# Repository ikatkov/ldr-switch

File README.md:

# Tiny LDR switch

Based on $0.60 Attiny13 MCU. 1kB flash, 256B ram.

It turns ON when it's dark (user configurable), stays ON for X hours, turns OFF, and waits till it's dark again. Intended to use with a battery, so it only consumes 5uA. Watch out for input power voltage. Min is 1.8V max is 5.5V. Max load current ~2A. Exceeds this and PCB traces will heat up and unsolder components.
There is simple diode craw-bar reverse voltage protection for MCU.

# Manufacturing

[PCB](./kicad/main.step)

[Enclosure lid](lid.stl)

[Enclosure base](base.stl)

# Code

MCU sleeps all the time. Wakes up via watchdog interrupt every 4 sec to measure light. It powers the LDR/R voltage divider via the MCU pin, takes ADC measurements, and turns off the pin to save power. Compares measured light with the thresholds and goes into ON, OFF, or WAIT_FOR_RESET state. Depending on the state, it turns the load ON/OFF.
A short button press wakes it from sleep, forcing it to measure light. 

* If it was in the OFF state - record the new "dark" light threshold, turn the load ON, start the auto-turn-off timer, and go into the ON state.
* If it was in the ON state - it turns the load OFF and goes into the WAIT_FOR_RESET state.

A long button press lets you set the auto-turn-off timer duration. Keep the button pressed and watch the LOAD blink. 1 blink == 1 hour, 2 blinks == 2 hours etc. Release the button once the desired number of hours is indicated. 

When the timer is UP, the load turns OFF, and the MCU transitions into the WAIT_FOR_RESET state.

There are two light thresholds in the code. 

* "dark" - once it's darker than this, MCU turns the load ON and goes into the ON state
* "bright" - once it's brighter than this, MCU goes from  WAIT_FOR_RESET into the OFF state. 

WAIT_FOR_RESET is meant to capture the daytime reset so that the switch is only active once per day for X hours.

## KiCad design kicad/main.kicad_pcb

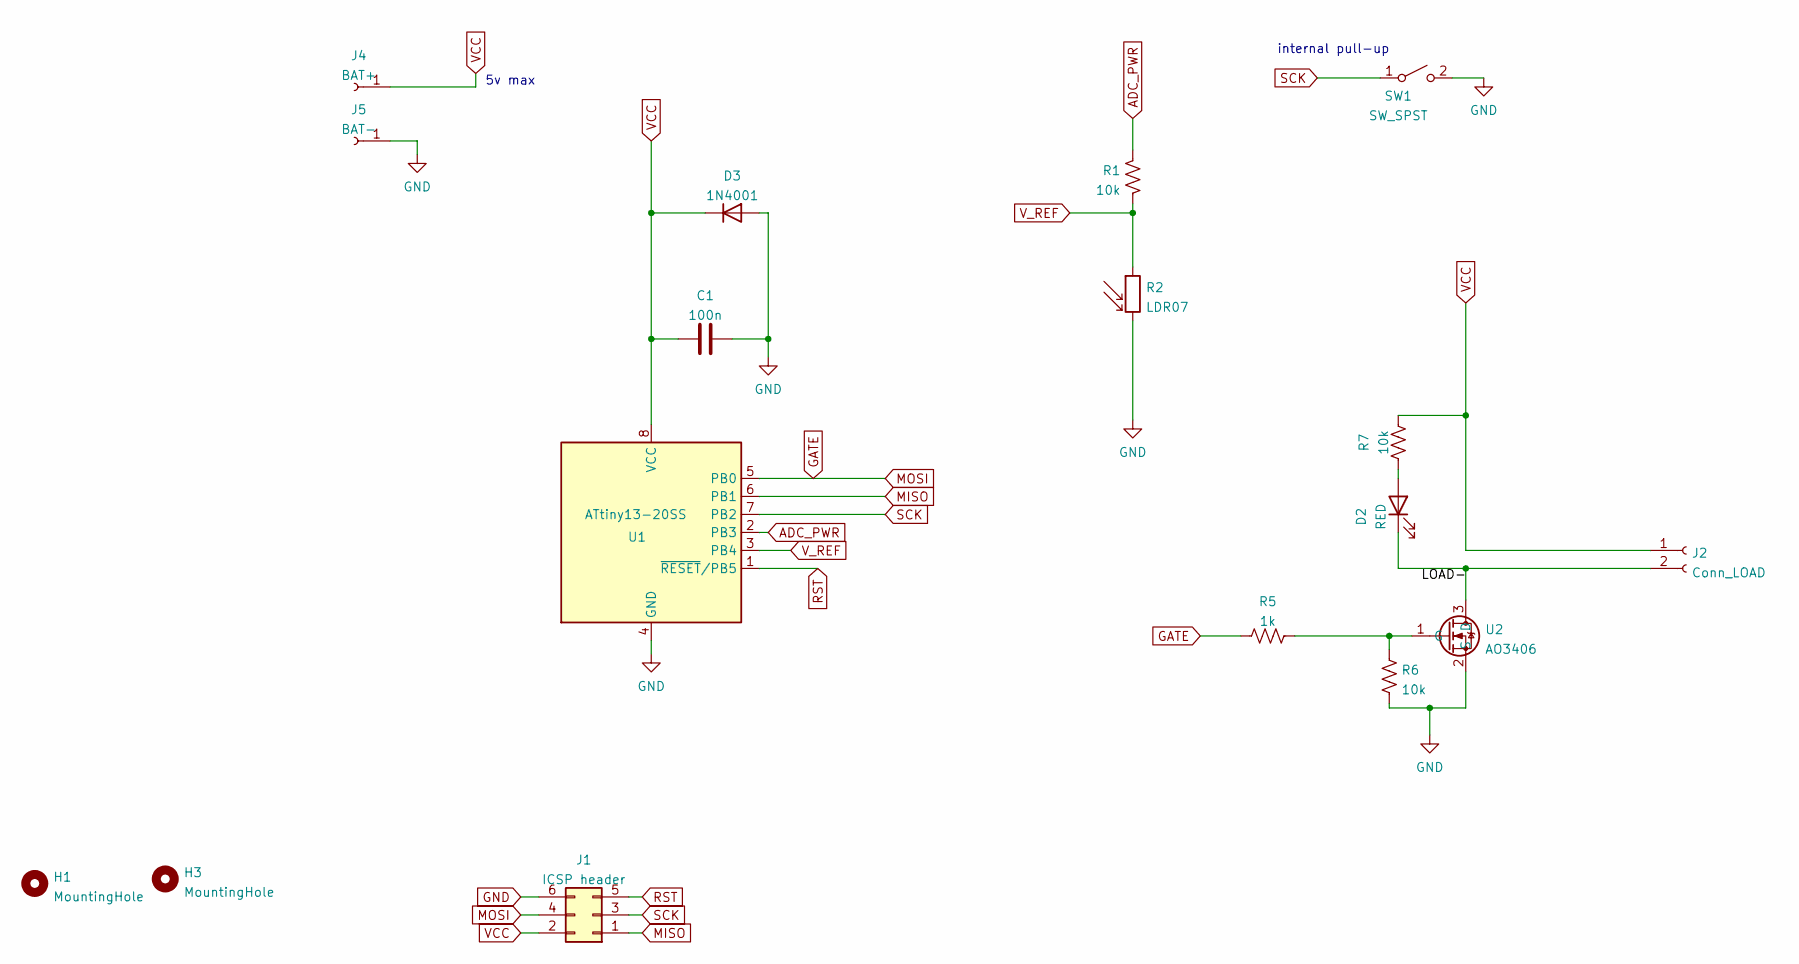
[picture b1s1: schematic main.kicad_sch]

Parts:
C1: 100n; C_1206_3216Metric
D2: RED; LED_0805_2012Metric
D3: 1N4001; D_SMA
H1, H3: MountingHole; MountingHole_2.2mm_M2
J1: ICSP header; PinHeader_2x03_P2.54mm_Vertical
J2: Conn_LOAD; JST_XH_B2B-XH-A_1x02_P2.50mm_Vertical
J4: BAT+; Pin_D1.0mm_L10.0mm
J5: BAT-; Pin_D1.0mm_L10.0mm
R1, R6, R7: 10k; R_0805_2012Metric
R2: LDR07; R_LDR_5.1x4.3mm_P3.4mm_Vertical
R5: 1k; R_0805_2012Metric
SW1: SW_SPST; SW_PUSH_6mm
U1: ATtiny13-20SS; SOIC-8_3.9x4.9mm_P1.27mm
U2: AO3406; SOT-23

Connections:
ADC_PWR: R1.2, U1.2 (PB3)
GATE: J1.4, R5.2, U1.5 (PB0)
GND: C1.2, D3.2 (A), J5.1, R2.2, R6.1, SW1.2 (B), U1.4 (GND), U2.2 (S)
MISO: J1.1, U1.6 (PB1)
unnamed: D2.1 (K), J2.2, U2.3 (D)
unnamed: D2.2 (A), R7.1
unnamed: R5.1, R6.2, U2.1 (G)
RST: J1.5, U1.1 (~RESET/PB5)
SCK: J1.3, SW1.1 (A), U1.7 (PB2)
VCC: C1.1, D3.1 (K), J1.2, J2.1, J4.1, R7.2, U1.8 (VCC)
V_REF: R1.1, R2.1, U1.3 (PB4)

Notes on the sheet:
internal pull-up
5v max

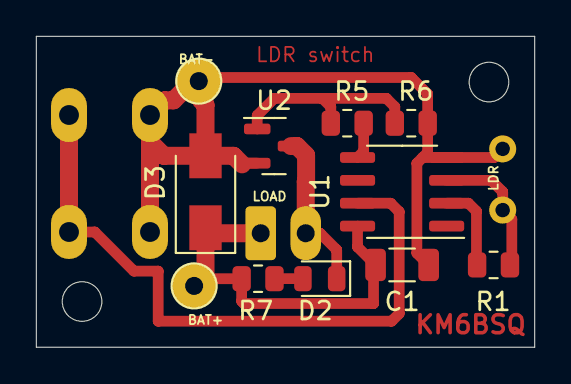
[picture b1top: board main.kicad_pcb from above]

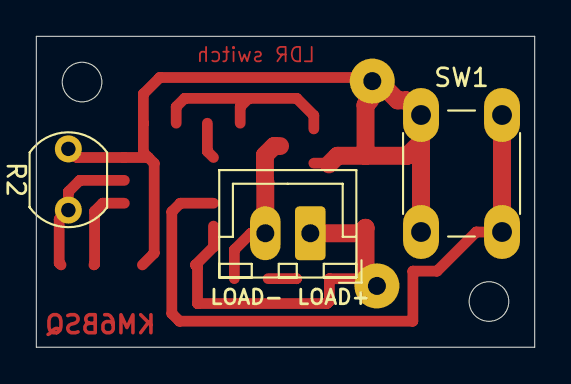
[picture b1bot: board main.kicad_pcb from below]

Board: 4 copper layers, 27.7 x 17.3 mm, 16 parts (3 on the bottom side), 9 nets.

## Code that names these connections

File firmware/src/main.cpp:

#include "Arduino.h"
#include <EEPROM.h>
#include <avr/sleep.h>
#include <avr/wdt.h>

static uint8_t lighOnDurationHours = 2;

#define LOAD_PIN PB0      // pin5 Attiny13
#define ADC_POWER_PIN PB3 //  pin2 on Attiny13
#define ADC_PIN A2        // PB4, pin3 Attiny13
#define INT_PIN PB2       // also button pin, pin7 Attiny13

static uint16_t lightThresholdDark = 700;
#define lightThresholdBright 350
#define LIGHT_THRESHOLD_HYSTERESIS 10

static enum state_t {
    OFF,
    ON,
    WAIT_FOR_RESET
} STATE;

static int32_t timer_sec = 0;

template <class T>
int EEPROM_writeAnything(int address, const T &value)
{
    const byte *p = (const byte *)(const void *)&value;
    uint8_t i;
    for (i = 0; i < sizeof(value); i++)
        EEPROM.write(address++, *p++);
    return i;
}

template <class T>
int EEPROM_readAnything(int address, T &value)
{
    byte *p = (byte *)(void *)&value;
    uint16_t i;
    for (i = 0; i < sizeof(value); i++)
        *p++ = EEPROM.read(address++);
    return i;
}

void powerDown(uint8_t sleepTime);
void blink(uint8_t times, uint16_t delayTime = 200);
void configureButtonInterrupt(bool enable);

EMPTY_INTERRUPT(PCINT0_vect);
EMPTY_INTERRUPT(WDT_vect)

void setlighOnDurationHours()
{
    uint8_t counter = 0;
    while (digitalRead(INT_PIN) == LOW)
    {
        counter++;
        if (counter > 8)
            counter = 1;
        blink(counter);
        delay(2000);
    }
    if (counter > 0 && counter != lighOnDurationHours)
    {
        lighOnDurationHours = counter;
        EEPROM_writeAnything(2, lighOnDurationHours);
    }
}

void readButton(uint16_t lightLevel)
{
    if (digitalRead(INT_PIN) == LOW)
    {
        if (STATE == ON)
        {
            digitalWrite(LOAD_PIN, LOW);
            STATE = WAIT_FOR_RESET;
            delay(2000); // debounce
        }
        else if (STATE == OFF || STATE == WAIT_FOR_RESET)
        {
            STATE = ON;
            blink(lighOnDurationHours);
            delay(1000); // blink delay + debounce
            digitalWrite(LOAD_PIN, HIGH);
            timer_sec = lighOnDurationHours * 60 * 60;

            // set new lightThresholdDark
            lightThresholdDark = lightLevel;

            EEPROM_writeAnything(0, lightThresholdDark);
        }
        setlighOnDurationHours();
    }
}

void powerDown(uint8_t sleepTime)
{
    ADCSRA &= ~(1 << ADEN); // adc OFF
    wdt_enable(sleepTime);  // watchdog
    WDTCR |= _BV(WDTIE);

    do
    {
        set_sleep_mode(SLEEP_MODE_PWR_DOWN);
        cli(); // Disable interrupts
        sleep_enable();
        sleep_bod_disable();
        sei(); // Enable interrupts
        sleep_cpu();

        sleep_disable();
        sei();
    } while (0);

    ADCSRA |= (1 << ADEN); // adc ON
}

void blink(uint8_t times, uint16_t delayTime)
{
    for (int i = times; i > 0; i--)
    {
        digitalWrite(LOAD_PIN, HIGH);
        delay(delayTime);
        digitalWrite(LOAD_PIN, LOW);
        delay(delayTime);
        wdt_reset();
    }
}

void setup()
{
    pinMode(ADC_POWER_PIN, OUTPUT);
    pinMode(ADC_PIN, INPUT);        // ADC
    pinMode(INT_PIN, INPUT_PULLUP); // button
    pinMode(LOAD_PIN, OUTPUT);      // gate

    analogReference(DEFAULT);

    cli();
    GIMSK |= _BV(PCIE);   //  Enable PCINT interrupt in the general interrupt mask
    PCMSK |= _BV(PCINT2); // Enable interrupt handler (ISR) for our chosen interrupt pin (PCINT2/PB2/pin 7)
    sei();

    EEPROM_readAnything(0, lightThresholdDark);
    if (lightThresholdDark < 0 || lightThresholdDark > 1024)
    {
        lightThresholdDark = 700;
        EEPROM_writeAnything(0, lightThresholdDark);
    }
    EEPROM_readAnything(2, lighOnDurationHours);
    if (lighOnDurationHours < 1 || lighOnDurationHours > 8)
    {
        lighOnDurationHours = 2;
    }

    blink(lighOnDurationHours);
}

void loop()
{
    digitalWrite(ADC_POWER_PIN, HIGH);
    uint16_t lightLevel = analogRead(ADC_PIN);
    digitalWrite(ADC_POWER_PIN, LOW);
    readButton(lightLevel);

    if (STATE == WAIT_FOR_RESET && lightLevel <= lightThresholdBright)
    {
        STATE = OFF;
    }

    if (STATE == OFF && lightLevel >= lightThresholdDark)
    {
        digitalWrite(LOAD_PIN, HIGH);
        timer_sec = lighOnDurationHours * 60 * 60;
        STATE = ON;
    }
    else if (STATE == ON && timer_sec <= 0)
    {
        digitalWrite(LOAD_PIN, LOW);
        STATE = WAIT_FOR_RESET;
    }
    else if (STATE == ON && lightLevel < lightThresholdDark - LIGHT_THRESHOLD_HYSTERESIS)
    {
        digitalWrite(LOAD_PIN, LOW);
        STATE = OFF;
    }

    powerDown(WDTO_4S);
    if (timer_sec > 0)
    {
        timer_sec -= 4;
    }
}

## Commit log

2022-11-09 code is broken, pcb OK
2022-11-09 working code, lots of comments
2022-11-09 attiny13 changes
2022-11-10 light duration settings
2022-11-10 clean up
2022-11-10 add README description and images
2022-11-10 grammar
2022-11-10 readme update
2022-11-10 add enclosure files
2022-11-10 link fixes
2022-11-10 formatting
2022-11-10 code clean up
